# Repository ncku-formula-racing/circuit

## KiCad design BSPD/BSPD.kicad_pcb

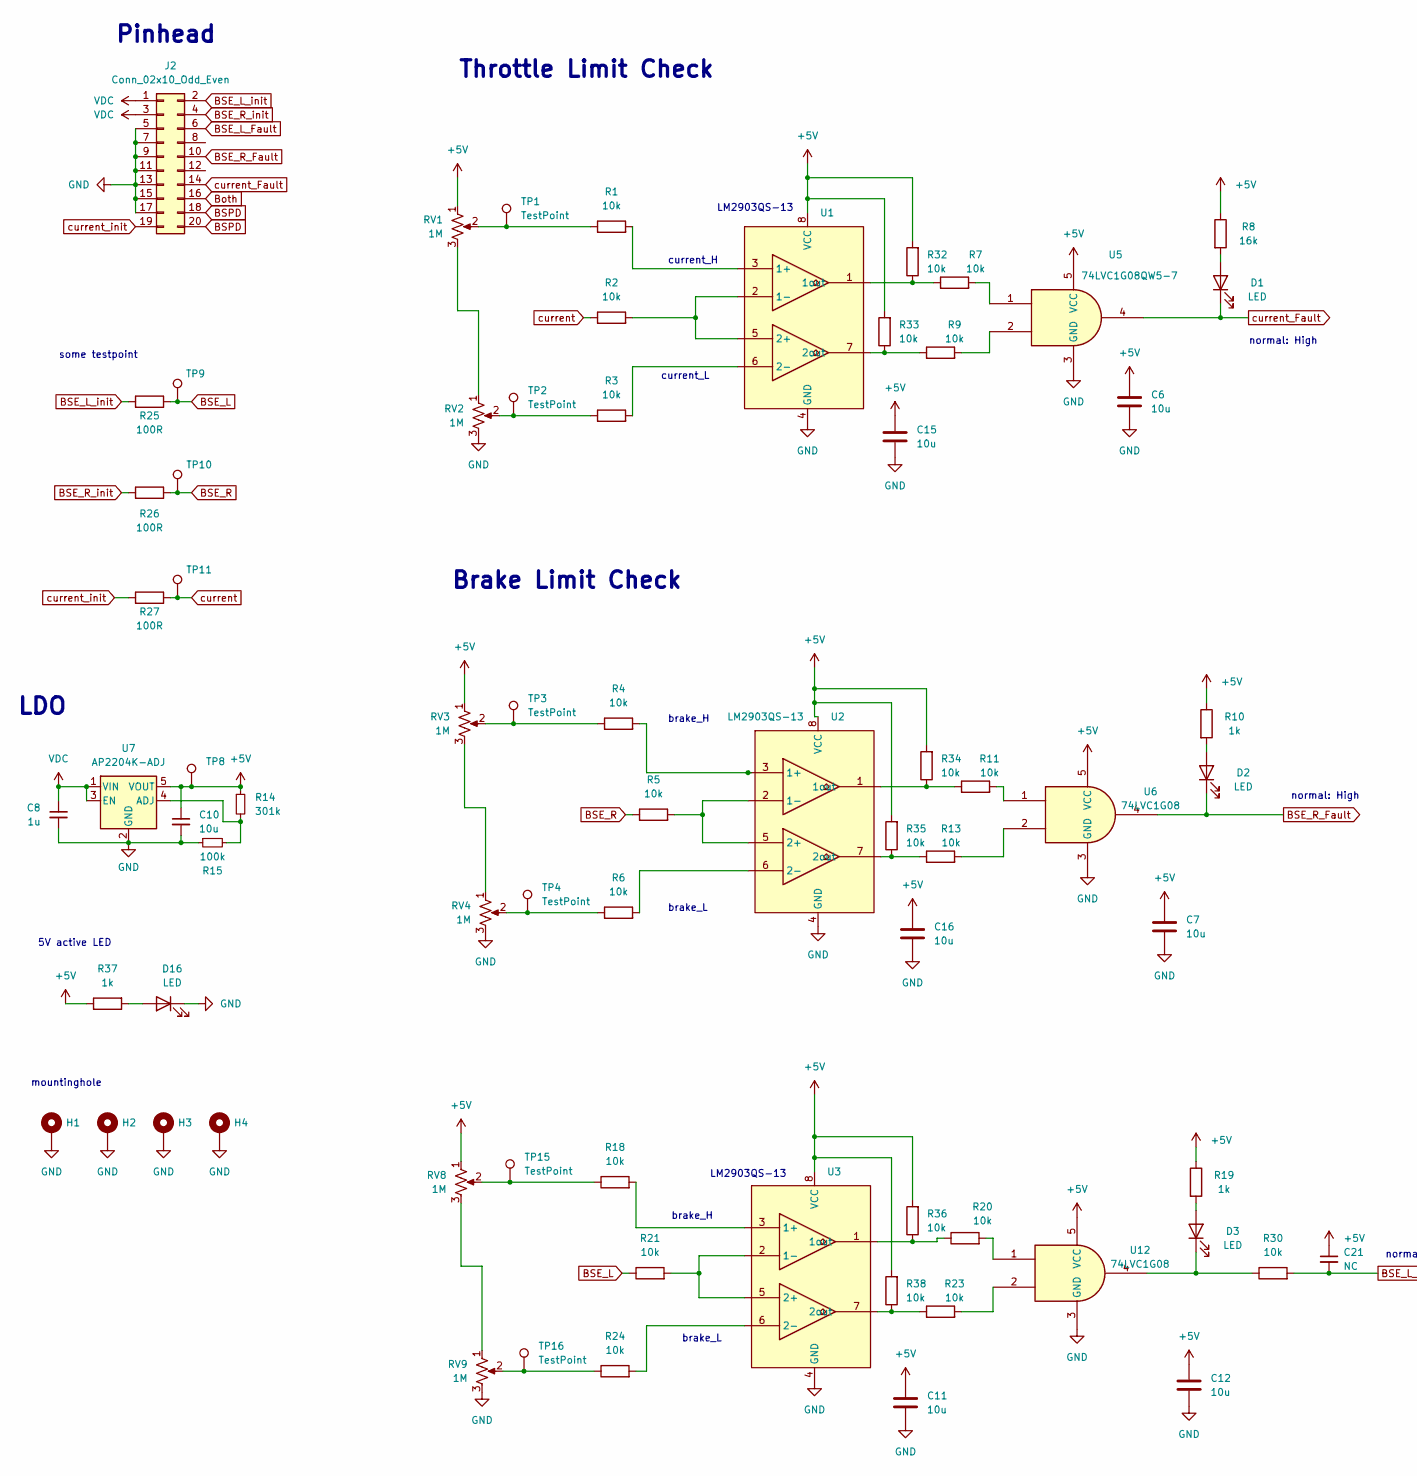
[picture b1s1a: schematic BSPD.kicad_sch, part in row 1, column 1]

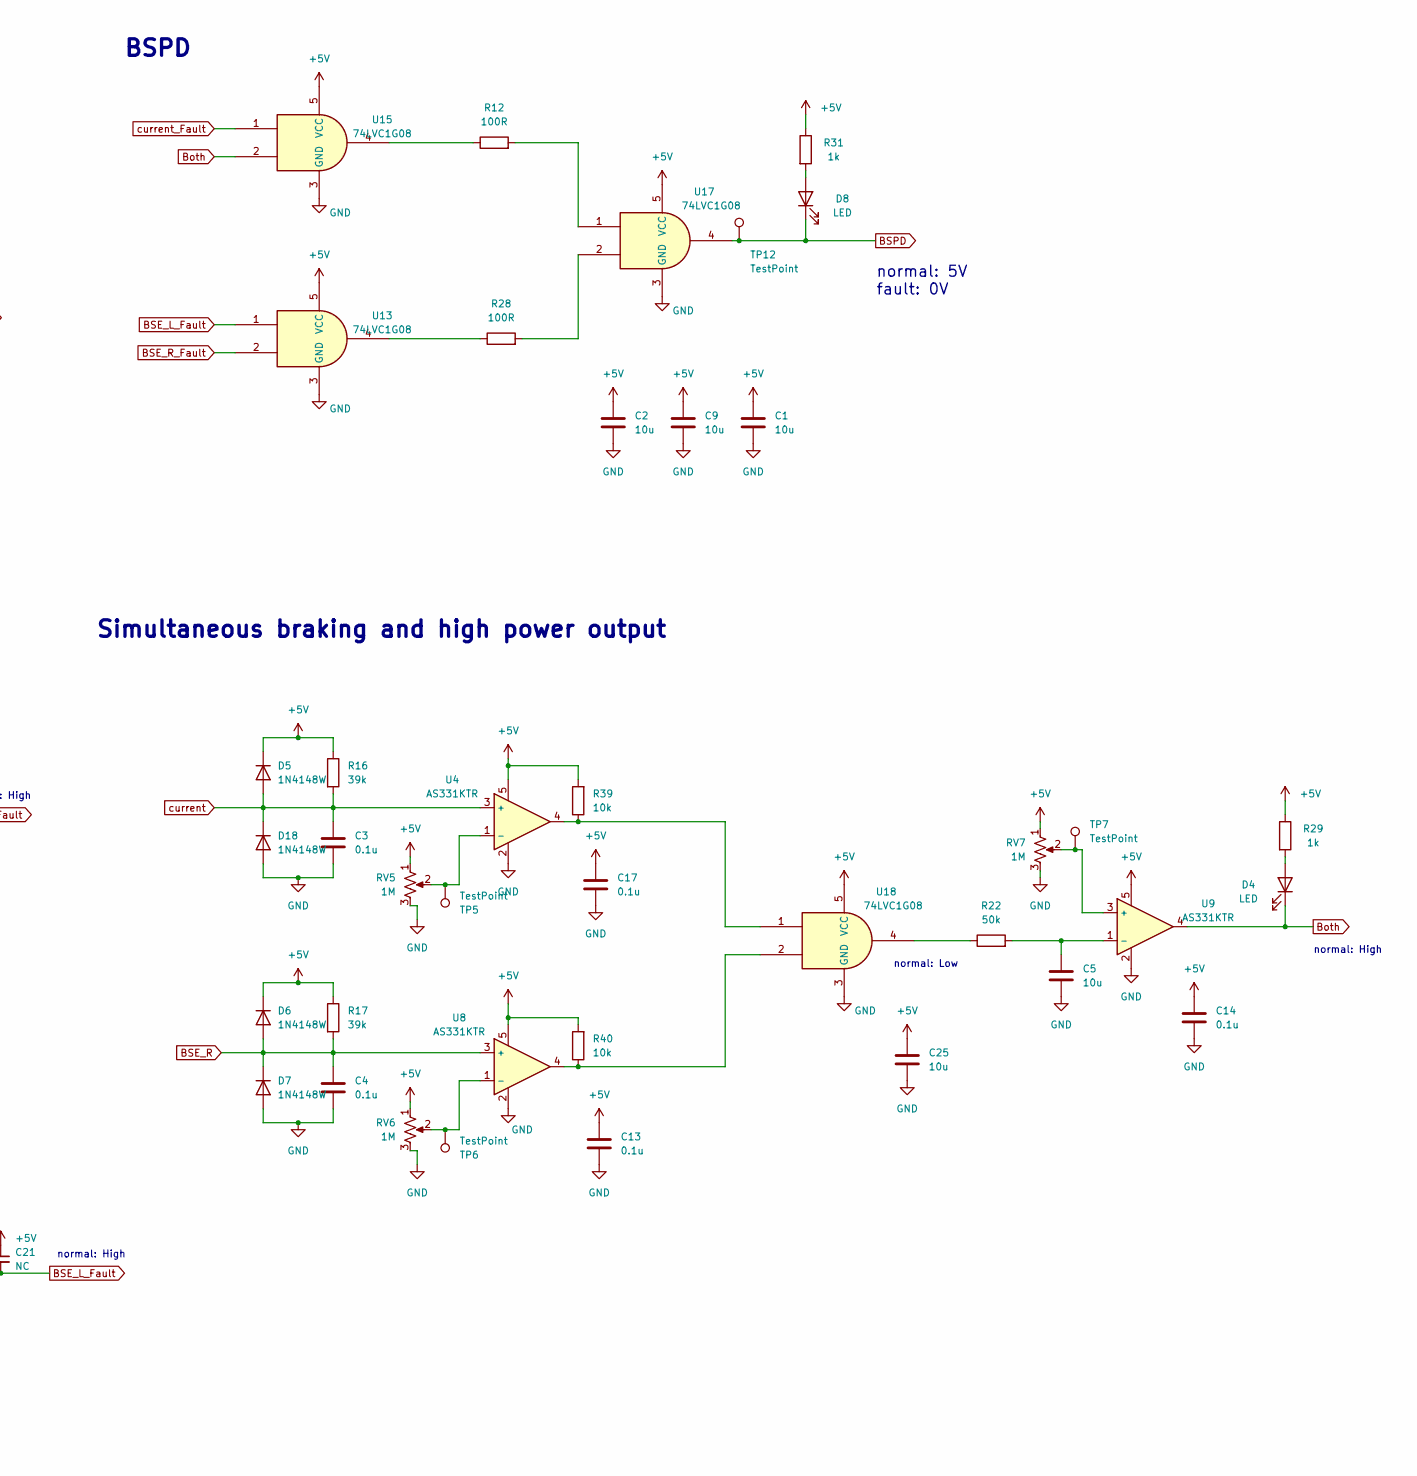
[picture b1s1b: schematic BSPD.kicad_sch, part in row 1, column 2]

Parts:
C1, C2, C5, C6, C7, C9, C10, C11, C12, C15, C16, C25: 10u; C_0805_2012Metric
C3, C4, C13, C14, C17: 0.1u; C_0603_1608Metric
C8: 1u; C_0603_1608Metric
C21: NC; C_Disc_D3.0mm_W1.6mm_P2.50mm
D1, D2, D3, D4, D8, D16: LED; LED_0805_2012Metric_Pad1.15x1.40mm_HandSolder
D5, D6, D7, D18: 1N4148W; D_SOD-123
H1, H2, H3, H4: MountingHole_Pad; MountingHole_3.2mm_M3_ISO7380_Pad
J2: Conn_02x10_Odd_Even; PinHeader_2x10_P2.54mm_Vertical
R1, R2, R3, R4, R5, R6, R7, R9, R11, R13, R18, R20, R21, R23, R24, R30, R32, R33, R34, R35, R36, R38, R39, R40: 10k; R_0603_1608Metric
R8: 16k; R_0603_1608Metric
R10, R19, R29, R31: 1k; R_0603_1608Metric
R12, R25, R26, R27, R28: 100R; R_0603_1608Metric
R14: 301k; R_0603_1608Metric
R15: 100k; R_0603_1608Metric
R16, R17: 39k; R_0603_1608Metric
R22: 50k; R_0603_1608Metric
R37: 1k; R_0603_1608Metric_Pad0.98x0.95mm_HandSolder
RV1, RV2, RV3, RV4, RV5, RV6, RV7, RV8, RV9: 1M; Potentiometer_Bourns_3296W_Vertical
TP1, TP2, TP3, TP4, TP5, TP6, TP7, TP8, TP9, TP10, TP11, TP12, TP15, TP16: TestPoint; TestPoint_THTPad_D1.5mm_Drill0.7mm
U1, U3: SO-8_3.9x4.9mm_P1.27mm
U2: LM2903QS-13; SO-8_3.9x4.9mm_P1.27mm
U4, U8, U9: AS331KTR; SOT-23-5
U5: 74LVC1G08QW5-7; SOT-23-5
U6, U12, U13, U15, U17, U18: 74LVC1G08; SOT-23-5
U7: AP2204K-ADJ; SOT-23-5

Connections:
+5V: C1.1, C2.1, C6.1, C7.1, C9.1, C10.1, C11.1, C12.1, C13.1, C14.1, C15.1, C16.1, C17.1, C21.1, C25.1, D5.1 (K), D6.1 (K), R8.1, R10.1, R14.1, R16.1, R17.1, R19.1, R29.1, R31.1, R32.2, R33.2, R34.2, R35.2, R36.2, R37.1, R38.2, R39.2, R40.2, RV1.1, RV3.1, RV5.1, RV6.1, RV7.1, RV8.1, TP8.1, U1.8 (VCC), U2.8 (VCC), U3.8 (VCC), U4.5, U5.5 (VCC), U6.5 (VCC), U7.5 (VOUT), U8.5, U9.5, U12.5 (VCC), U13.5 (VCC), U15.5 (VCC), U17.5 (VCC), U18.5 (VCC)
BSE_L: R21.1, R25.1, TP9.1
BSE_L_Fault: C21.2, J2.6, R30.2, U13.1
BSE_L_init: J2.2, R25.2
BSE_R: C4.1, D6.2 (A), D7.1 (K), R5.1, R17.2, R26.1, TP10.1, U8.3 (+)
BSE_R_Fault: D2.1 (K), J2.10, U6.4, U13.2
BSE_R_init: J2.4, R26.2
BSPD: D8.1 (K), J2.18, J2.20, TP12.1, U17.4
Both: D4.1 (K), J2.16, U9.4, U15.2
GND: C1.2, C2.2, C3.2, C4.2, C5.2, C6.2, C7.2, C8.2, C9.2, C10.2, C11.2, C12.2, C13.2, C14.2, C15.2, C16.2, C17.2, C25.2, D7.2 (A), D16.1 (K), D18.2 (A), H1.1, H2.1, H3.1, H4.1, J2.5, J2.7, J2.9, J2.11, J2.13, J2.15, J2.17, R15.1, RV2.3, RV4.3, RV5.3, RV6.3, RV7.3, RV9.3, U1.4 (GND), U2.4 (GND), U3.4 (GND), U4.2, U5.3 (GND), U6.3 (GND), U7.2 (GND), U8.2, U9.2, U12.3 (GND), U13.3 (GND), U15.3 (GND), U17.3 (GND), U18.3 (GND)
unnamed: D1.2 (A), R8.2
unnamed: D2.2 (A), R10.2
unnamed: D3.2 (A), R19.2
unnamed: D3.1 (K), R30.1, U12.4
unnamed: D4.2 (A), R29.2
unnamed: D8.2 (A), R31.2
unnamed: D16.2 (A), R37.2
unnamed: R1.1, RV1.2, TP1.1
unnamed: R3.1, RV2.2, TP2.1
unnamed: R4.1, RV3.2, TP3.1
unnamed: R6.1, RV4.2, TP4.1
unnamed: R7.2, U5.1
unnamed: R9.2, U5.2
unnamed: R11.2, U6.1
unnamed: R12.1, U15.4
unnamed: R12.2, U17.1
unnamed: R13.2, U6.2
unnamed: R18.1, RV8.2, TP15.1
unnamed: R20.2, U12.1
unnamed: R22.1, U18.4
unnamed: R23.2, U12.2
unnamed: R24.1, RV9.2, TP16.1
unnamed: R28.1, U13.4
unnamed: R28.2, U17.2
unnamed: R39.1, U4.4, U18.1
unnamed: R40.1, U8.4, U18.2
unnamed: RV1.3, RV2.1
unnamed: RV3.3, RV4.1
unnamed: RV8.3, RV9.1
unnamed: R1.2, U1.3 (1+)
unnamed: R2.2, U1.2 (1-), U1.5 (2+)
unnamed: R7.1, R32.1, U1.1 (1out)
unnamed: R3.2, U1.6 (2-)
unnamed: R9.1, R33.1, U1.7 (2out)
unnamed: R4.2, U2.3 (1+)
unnamed: R5.2, U2.2 (1-), U2.5 (2+)
unnamed: R11.1, R34.1, U2.1 (1out)
unnamed: R6.2, U2.6 (2-)
unnamed: R13.1, R35.1, U2.7 (2out)
unnamed: R18.2, U3.3 (1+)
unnamed: R21.2, U3.2 (1-), U3.5 (2+)
unnamed: R20.1, R36.1, U3.1 (1out)
unnamed: R24.2, U3.6 (2-)
unnamed: R23.1, R38.1, U3.7 (2out)
unnamed: RV5.2, TP5.1, U4.1 (-)
unnamed: R14.2, R15.2, U7.4 (ADJ)
unnamed: RV6.2, TP6.1, U8.1 (-)
unnamed: RV7.2, TP7.1, U9.3 (+)
unnamed: C5.1, R22.2, U9.1 (-)
VDC: C8.1, J2.1, J2.3, U7.1 (VIN), U7.3 (EN)
current: C3.1, D5.2 (A), D18.1 (K), R2.1, R16.2, R27.1, TP11.1, U4.3 (+)
current_Fault: D1.1 (K), J2.14, U5.4, U15.1
current_init: J2.19, R27.2

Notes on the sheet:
brake_H
normal: 5V fault: 0V
normal: High
BSPD
Throttle Limit Check
current_H
current_L
Pinhead
brake_L
Simultaneous braking and high power output
normal: Low
some testpoint
LM2903QS-13
mountinghole
Brake Limit Check
LDO
5V active LED

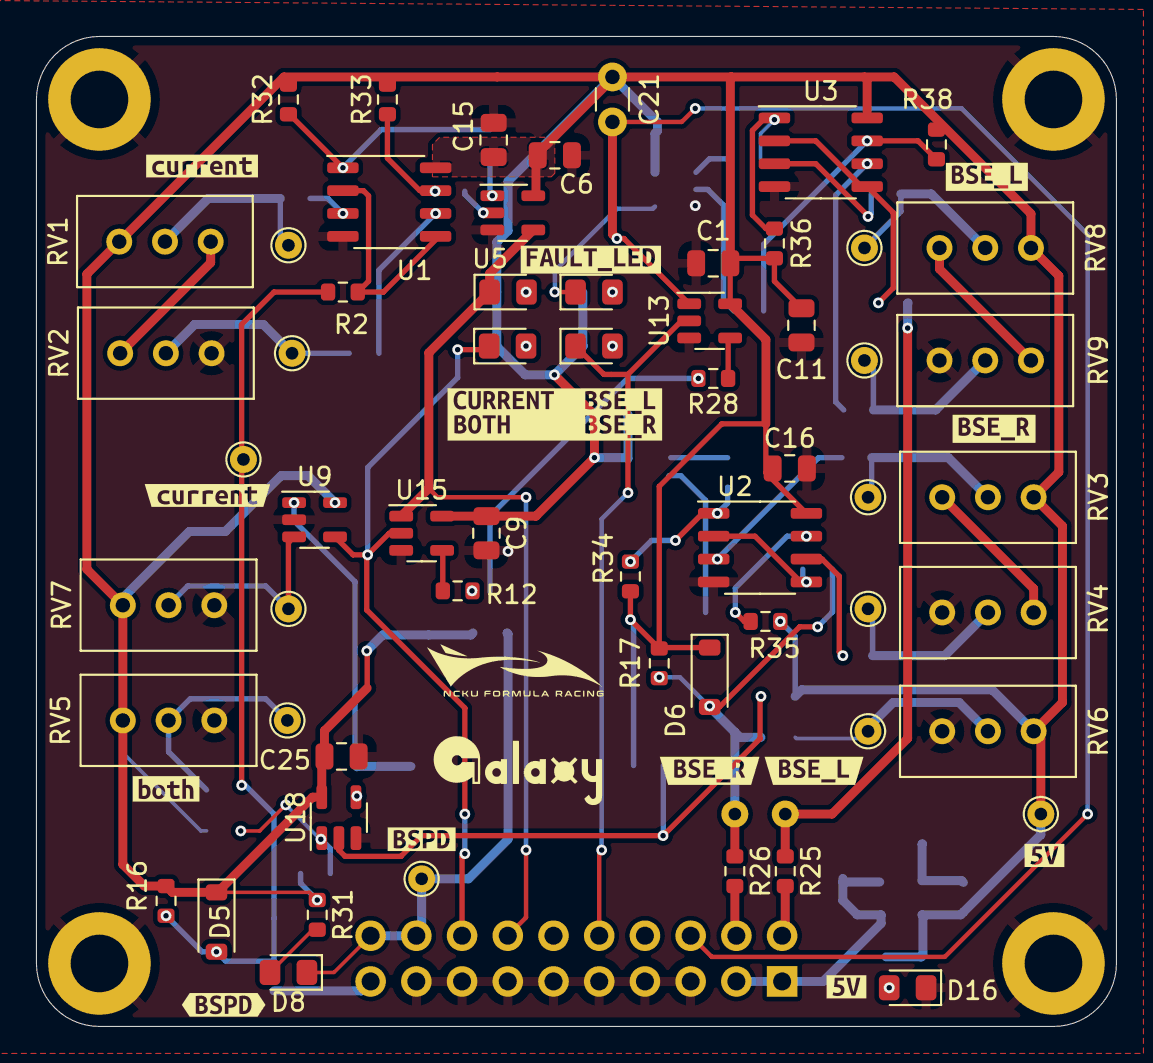
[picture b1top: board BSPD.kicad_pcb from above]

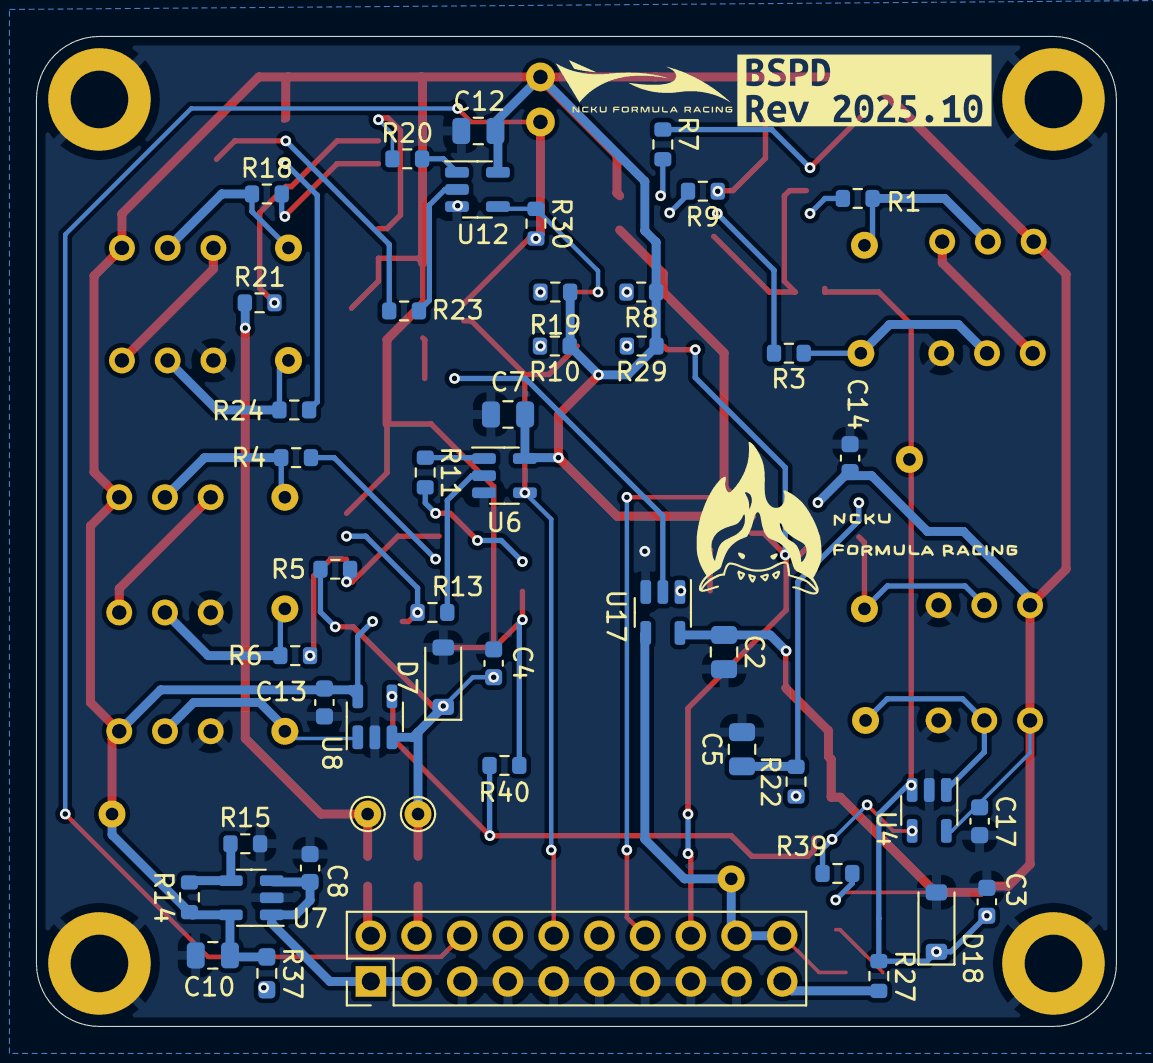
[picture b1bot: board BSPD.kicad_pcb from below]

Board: 2 copper layers, 60.0 x 55.0 mm, 125 parts (49 on the bottom side), 63 nets.

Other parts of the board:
kibuzzard-68E66274: G***; kibuzzard-68E66274
kibuzzard-681DF91B: G***; kibuzzard-681DF91B
kibuzzard-681DF95E: G***; kibuzzard-681DF95E
kibuzzard-681DF96B: G***; kibuzzard-681DF96B
kibuzzard-681DF708: G***; kibuzzard-681DF708
kibuzzard-681DF939: G***; kibuzzard-681DF939
kibuzzard-681DFA90: G***; kibuzzard-681DFA90
kibuzzard-681DFAB1: G***; kibuzzard-681DFAB1
kibuzzard-681DFABC: G***; kibuzzard-681DFABC
kibuzzard-681DFAC8: G***; kibuzzard-681DFAC8
kibuzzard-681DFAF7: G***; kibuzzard-681DFAF7
kibuzzard-681DFB04: G***; kibuzzard-681DFB04
kibuzzard-681DFC5A: G***; kibuzzard-681DFC5A
kibuzzard-688B2CB5: G***; kibuzzard-688B2CB5

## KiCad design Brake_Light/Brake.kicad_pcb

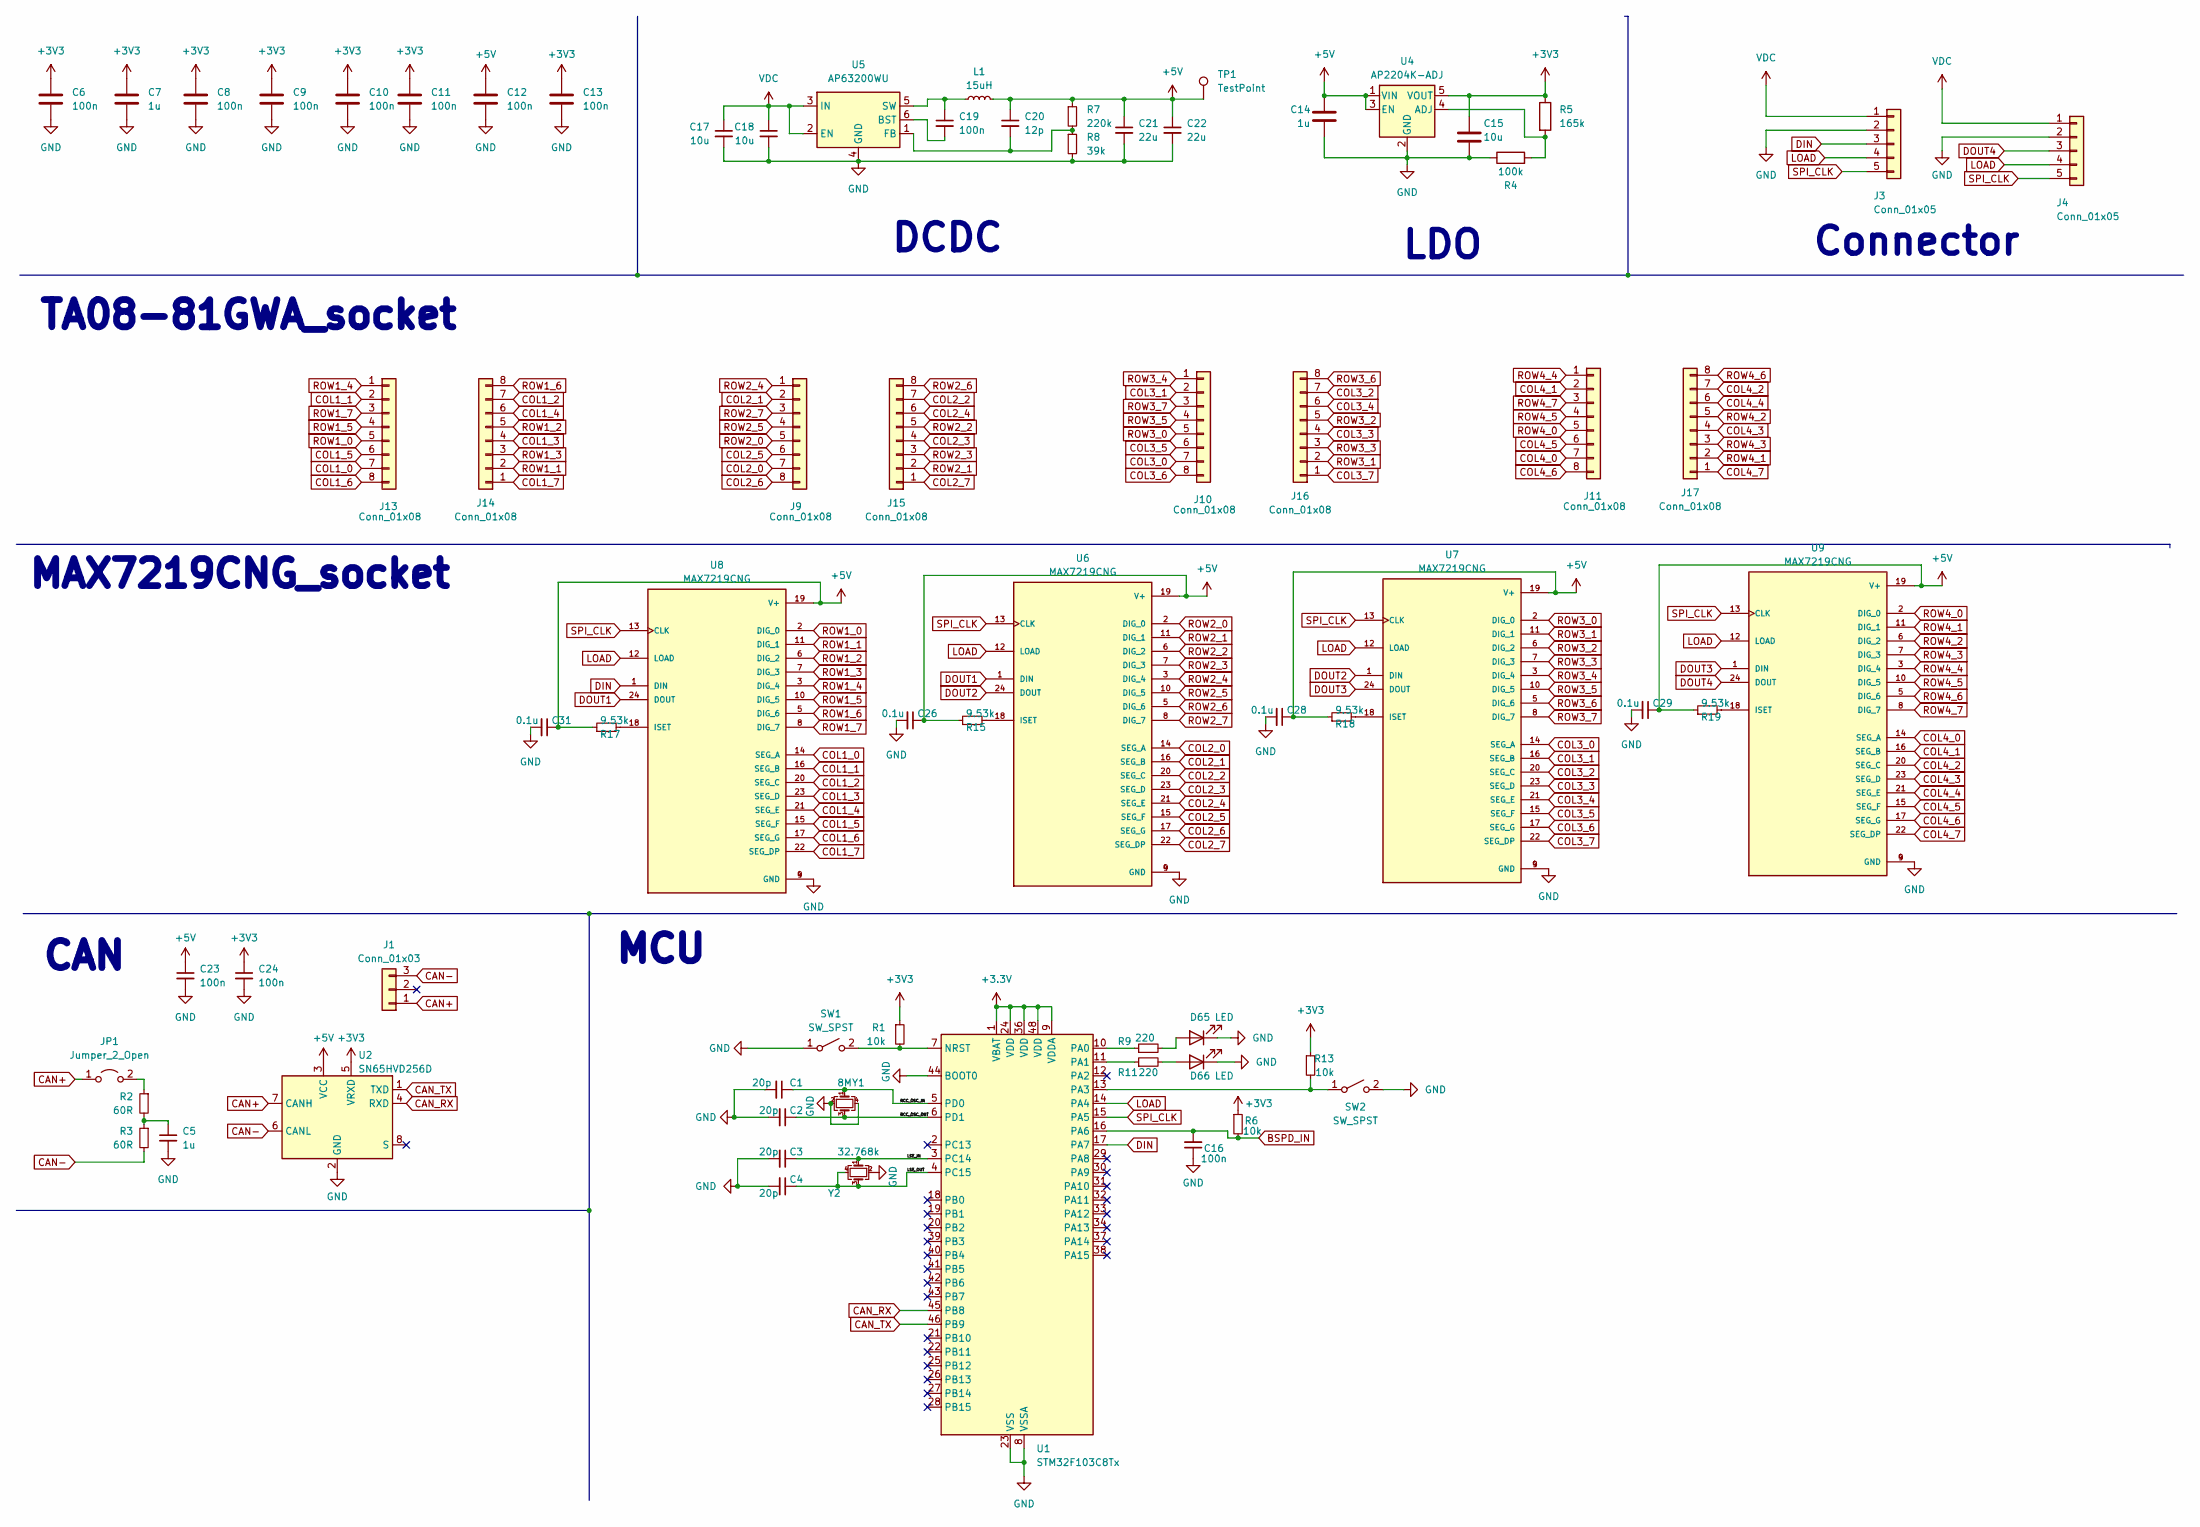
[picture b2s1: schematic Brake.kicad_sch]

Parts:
C1, C2, C3, C4: 20p; C_0603_1608Metric
C5: 1u; C_0603_1608Metric
C6, C8, C9, C10, C11, C12, C13: 100n; R_0603_1608Metric
C7, C14: 1u; R_0603_1608Metric
C15: 10u; R_0805_2012Metric
C16, C19, C23, C24: 100n; C_0603_1608Metric
C17, C18: 10u; C_0805_2012Metric
C20: 12p; C_0603_1608Metric
C21, C22: 22u; C_0805_2012Metric
C26, C28, C29, C31: 0.1u; C_0603_1608Metric
D65, D66: LED; LED_0603_1608Metric
J1: Conn_01x03; PinHeader_1x03_P2.54mm_Vertical
J3, J4: Conn_01x05; PinHeader_1x05_P2.54mm_Vertical
J9, J10, J11, J13, J14, J15, J16, J17: Conn_01x08; PinSocket_1x08_P2.54mm_Vertical
JP1: Jumper_2_Open; PinHeader_1x02_P2.54mm_Vertical
L1: 15uH; L_Coilcraft_XAL6060-XXX
R1, R6, R13: 10k; R_0603_1608Metric
R2, R3: 60R; R_0603_1608Metric
R4: 100k; R_0603_1608Metric
R5: 165k; R_0603_1608Metric
R7: 220k; R_0603_1608Metric
R8: 39k; R_0603_1608Metric
R9, R11: 220; R_0603_1608Metric
R15, R17, R18, R19: 9.53k; R_0603_1608Metric
SW1, SW2: SW_SPST; SW_SPST_FSMSM
TP1: TestPoint; TestPoint_THTPad_D1.5mm_Drill0.7mm
U1: STM32F103C8Tx; LQFP-48_7x7mm_P0.5mm
U2: SN65HVD256D; SOIC-8_3.9x4.9mm_P1.27mm
U4: AP2204K-ADJ; SOT-23-5
U5: AP63200WU; TSOT-23-6
U6, U7, U8, U9: MAX7219CNG; DIP-24_W7.62mm_Socket; PARTREV 6
Y1: 8M; Crystal_SMD_SeikoEpson_FA238-4Pin_3.2x2.5mm
Y2: 32.768k; Crystal_SMD_SeikoEpson_FA238-4Pin_3.2x2.5mm

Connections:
+3.3V: U1.1 (VBAT), U1.9 (VDDA), U1.24 (VDD), U1.36 (VDD), U1.48 (VDD)
+3V3: C6.1, C7.1, C8.1, C9.1, C10.1, C11.1, C13.1, C15.1, C24.1, R1.1, R5.1, R6.1, R13.1, U2.5 (VRXD), U4.5 (VOUT)
+5V: C12.1, C14.1, C20.1, C21.1, C22.1, C23.1, C26.1, C28.1, C29.1, C31.1, L1.2, R7.1, R15.1, R17.1, R18.1, R19.1, TP1.1, U2.3 (VCC), U4.1 (VIN), U4.3 (EN), U6.19 (V+), U7.19 (V+), U8.19 (V+), U9.19 (V+)
/LSE_IN: C3.1, U1.3 (PC14), Y2.1
/LSE_OUT: C4.1, U1.4 (PC15), Y2.3, Y2.4
/RCC_OSC_IN: C1.1, U1.5 (PD0), Y1.1
/RCC_OSC_OUT: C2.1, U1.6 (PD1), Y1.3
BSPD_IN: C16.2, R6.2, U1.16 (PA6)
CAN+: J1.1, JP1.1 (A), U2.7 (CANH)
CAN-: J1.3, R3.2, U2.6 (CANL)
CAN_RX: U1.45 (PB8), U2.4 (RXD)
CAN_TX: U1.46 (PB9), U2.1 (TXD)
COL1_0: J13.7, U8.14 (SEG_A)
COL1_1: J13.2, U8.16 (SEG_B)
COL1_2: J14.7, U8.20 (SEG_C)
COL1_3: J14.4, U8.23 (SEG_D)
COL1_4: J14.6, U8.21 (SEG_E)
COL1_5: J13.6, U8.15 (SEG_F)
COL1_6: J13.8, U8.17 (SEG_G)
COL1_7: J14.1, U8.22 (SEG_DP)
COL2_0: J9.7, U6.14 (SEG_A)
COL2_1: J9.2, U6.16 (SEG_B)
COL2_2: J15.7, U6.20 (SEG_C)
COL2_3: J15.4, U6.23 (SEG_D)
COL2_4: J15.6, U6.21 (SEG_E)
COL2_5: J9.6, U6.15 (SEG_F)
COL2_6: J9.8, U6.17 (SEG_G)
COL2_7: J15.1, U6.22 (SEG_DP)
COL3_0: J10.7, U7.14 (SEG_A)
COL3_1: J10.2, U7.16 (SEG_B)
COL3_2: J16.7, U7.20 (SEG_C)
COL3_3: J16.4, U7.23 (SEG_D)
COL3_4: J16.6, U7.21 (SEG_E)
COL3_5: J10.6, U7.15 (SEG_F)
COL3_6: J10.8, U7.17 (SEG_G)
COL3_7: J16.1, U7.22 (SEG_DP)
COL4_0: J11.7, U9.14 (SEG_A)
COL4_1: J11.2, U9.16 (SEG_B)
COL4_2: J17.7, U9.20 (SEG_C)
COL4_3: J17.4, U9.23 (SEG_D)
COL4_4: J17.6, U9.21 (SEG_E)
COL4_5: J11.6, U9.15 (SEG_F)
COL4_6: J11.8, U9.17 (SEG_G)
COL4_7: J17.1, U9.22 (SEG_DP)
DIN: J3.3, U1.17 (PA7), U8.1 (DIN)
DOUT1: U6.1 (DIN), U8.24 (DOUT)
DOUT2: U6.24 (DOUT), U7.1 (DIN)
DOUT3: U7.24 (DOUT), U9.1 (DIN)
DOUT4: J4.3, U9.24 (DOUT)
GND: C1.2, C2.2, C3.2, C4.2, C5.2, C6.2, C7.2, C8.2, C9.2, C10.2, C11.2, C12.2, C13.2, C14.2, C15.2, C16.1, C17.2, C18.2, C21.2, C22.2, C23.2, C24.2, C26.2, C28.2, C29.2, C31.2, D65.1 (K), D66.1 (K), J3.2, J4.2, R4.1, R8.2, SW1.1 (A), SW2.2 (B), U1.8 (VSSA), U1.23 (VSS), U1.35 (VSS), U1.44 (BOOT0), U1.47 (VSS), U2.2 (GND), U4.2 (GND), U5.4 (GND), U6.4 (GND), U6.9 (GND), U7.4 (GND), U7.9 (GND), U8.4 (GND), U8.9 (GND), U9.4 (GND), U9.9 (GND), Y1.2, Y1.4, Y2.2
LOAD: J3.4, J4.4, U1.14 (PA4), U6.12 (LOAD), U7.12 (LOAD), U8.12 (LOAD), U9.12 (LOAD)
unnamed: C5.1, R2.2, R3.1
unnamed: D65.2 (A), R9.2
unnamed: D66.2 (A), R11.2
unnamed: JP1.2 (B), R2.1
unnamed: R1.2, SW1.2 (B), U1.7 (NRST)
unnamed: R13.2, SW2.1 (A), U1.13 (PA3)
unnamed: R9.1, U1.10 (PA0)
unnamed: R11.1, U1.11 (PA1)
unnamed: R4.2, R5.2, U4.4 (ADJ)
unnamed: C19.2, U5.6 (BST)
unnamed: C20.2, R7.2, R8.1, U5.1 (FB)
unnamed: C19.1, L1.1, U5.5 (SW)
unnamed: R15.2, U6.18 (ISET)
unnamed: R18.2, U7.18 (ISET)
unnamed: R17.2, U8.18 (ISET)
unnamed: R19.2, U9.18 (ISET)
ROW1_0: J13.5, U8.2 (DIG_0)
ROW1_1: J14.2, U8.11 (DIG_1)
ROW1_2: J14.5, U8.6 (DIG_2)
ROW1_3: J14.3, U8.7 (DIG_3)
ROW1_4: J13.1, U8.3 (DIG_4)
ROW1_5: J13.4, U8.10 (DIG_5)
ROW1_6: J14.8, U8.5 (DIG_6)
ROW1_7: J13.3, U8.8 (DIG_7)
ROW2_0: J9.5, U6.2 (DIG_0)
ROW2_1: J15.2, U6.11 (DIG_1)
ROW2_2: J15.5, U6.6 (DIG_2)
ROW2_3: J15.3, U6.7 (DIG_3)
ROW2_4: J9.1, U6.3 (DIG_4)
ROW2_5: J9.4, U6.10 (DIG_5)
ROW2_6: J15.8, U6.5 (DIG_6)
ROW2_7: J9.3, U6.8 (DIG_7)
ROW3_0: J10.5, U7.2 (DIG_0)
ROW3_1: J16.2, U7.11 (DIG_1)
ROW3_2: J16.5, U7.6 (DIG_2)
ROW3_3: J16.3, U7.7 (DIG_3)
ROW3_4: J10.1, U7.3 (DIG_4)
ROW3_5: J10.4, U7.10 (DIG_5)
ROW3_6: J16.8, U7.5 (DIG_6)
ROW3_7: J10.3, U7.8 (DIG_7)
ROW4_0: J11.5, U9.2 (DIG_0)
ROW4_1: J17.2, U9.11 (DIG_1)
ROW4_2: J17.5, U9.6 (DIG_2)
ROW4_3: J17.3, U9.7 (DIG_3)
ROW4_4: J11.1, U9.3 (DIG_4)
ROW4_5: J11.4, U9.10 (DIG_5)
ROW4_6: J17.8, U9.5 (DIG_6)
ROW4_7: J11.3, U9.8 (DIG_7)
SPI_CLK: J3.5, J4.5, U1.15 (PA5), U6.13 (CLK), U7.13 (CLK), U8.13 (CLK), U9.13 (CLK)
VDC: C17.1, C18.1, J3.1, J4.1, U5.2 (EN), U5.3 (IN)

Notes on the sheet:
Connector
CAN
MAX7219CNG_socket
DCDC
TA08-81GWA_socket
LDO
MCU

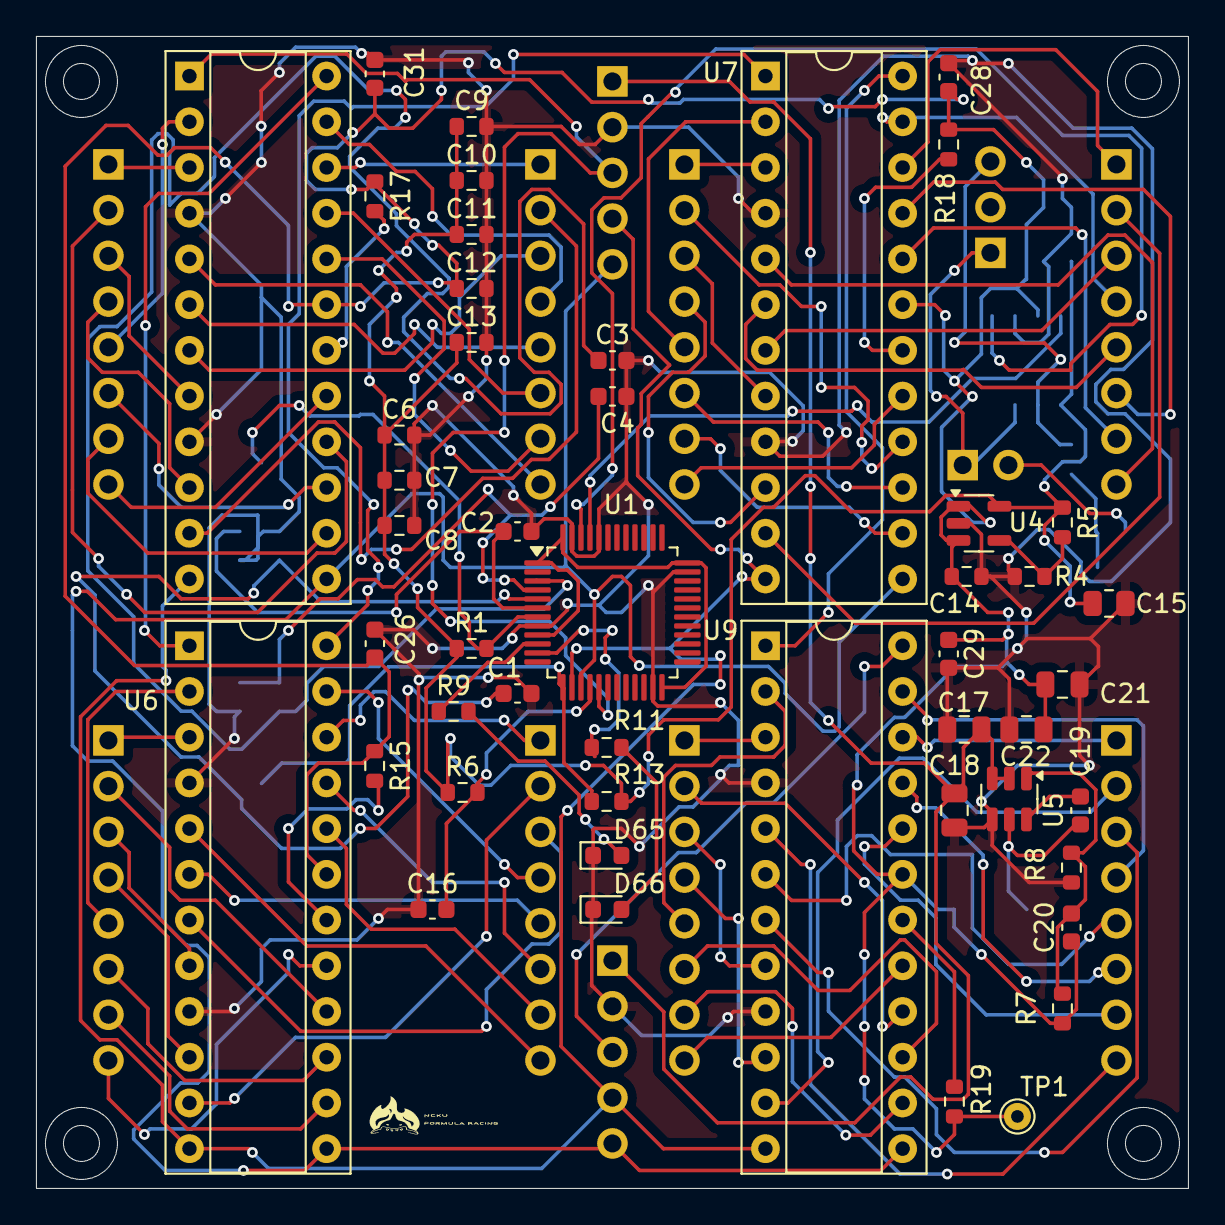
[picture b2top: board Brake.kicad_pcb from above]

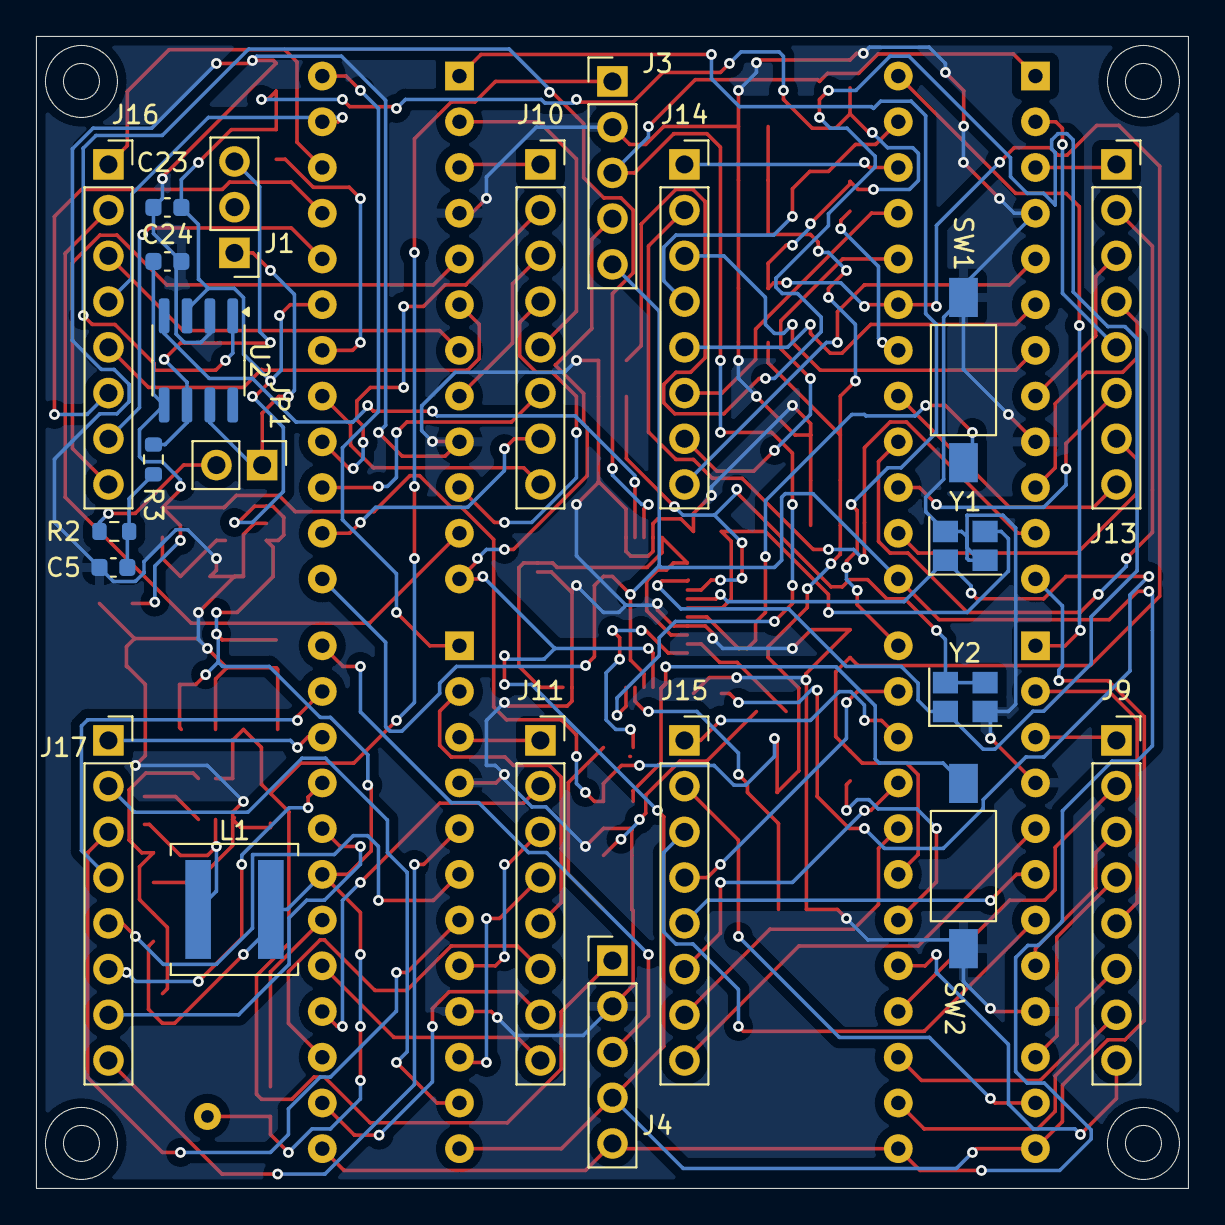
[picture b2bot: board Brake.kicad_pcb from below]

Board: 2 copper layers, 64.0 x 64.0 mm, 71 parts (23 on the bottom side), 101 nets.
